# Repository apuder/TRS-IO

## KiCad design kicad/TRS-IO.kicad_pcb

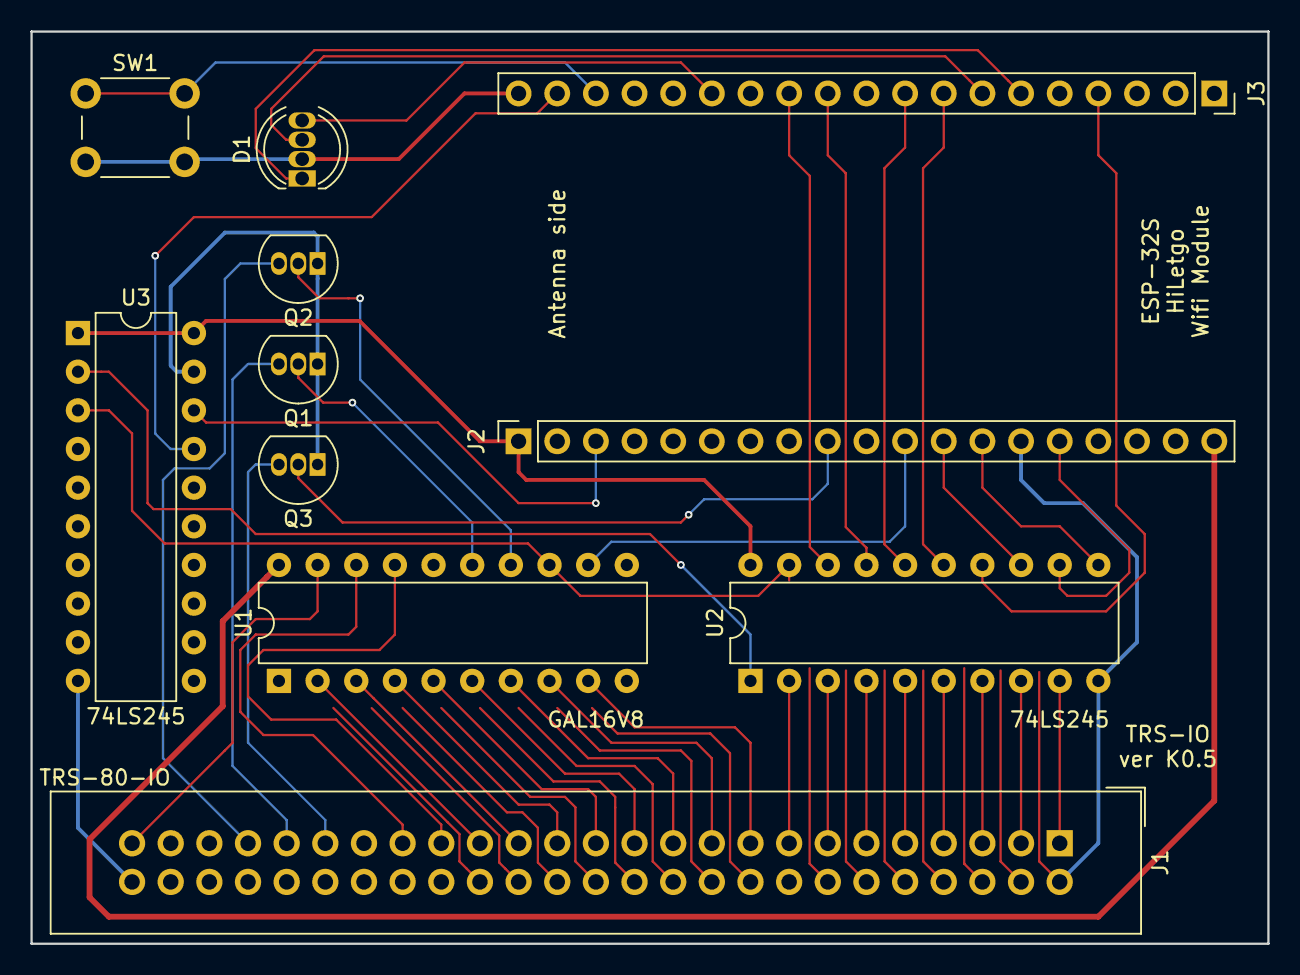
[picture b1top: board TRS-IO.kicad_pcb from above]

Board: 2 copper layers, 81.3 x 59.9 mm, 11 parts (0 on the bottom side), 45 nets.

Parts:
D1: LED_RCGB; LED_D5.0mm-4
J1: TRS-80-IO; IDC-Header_2x25_P2.54mm_Vertical
J2, J3: Conn_01x19; PinSocket_1x19_P2.54mm_Vertical
Q1, Q2, Q3: 2N7000; TO-92_Inline
SW1: SW_Push; SW_PUSH_6mm
U1: GAL16V8; DIP-20_W7.62mm
U2, U3: 74LS245; DIP-20_W7.62mm

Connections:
+3V3: J2.1, U2.20, U3.1, U3.20
+5V: J2.19, U1.20
GND: D1.2, J1.2, J1.4, J1.6, J1.8, J1.10, J1.12, J1.14, J1.16, J1.18, J1.20, J1.22, J1.24, J1.26, J1.28, J1.30, J1.32, J1.34, J1.36, J1.38, J1.40, J1.42, J1.44, J1.46, J1.48, J1.50, J2.14, J3.13, J3.19, Q1.1, Q2.1, Q3.1, SW1.2, U1.10, U2.10, U3.10, U3.19
unnamed: D1.1, J3.6
unnamed: D1.3, J3.7
unnamed: D1.4, J3.14
unnamed: J1.1, U2.9
unnamed: J1.3, U2.8
unnamed: J1.5, U2.7
unnamed: J1.7, U2.6
unnamed: J1.9, U2.5
unnamed: J1.11, U2.4
unnamed: J1.13, U2.3
unnamed: J1.15, U2.2
unnamed: J1.17, U1.9
unnamed: J1.19, U1.8
unnamed: J1.21, U1.7
unnamed: J1.23, U1.6
unnamed: J1.25, U1.5
unnamed: J1.27, U1.4
unnamed: J1.29, U1.3
unnamed: J1.31, U1.2
unnamed: J1.33, U1.17
unnamed: J1.35, U1.18
unnamed: J1.39, Q3.3
unnamed: J1.41, Q1.3
unnamed: J1.43, Q2.3
unnamed: J1.49, U1.19
unnamed: J2.3, U3.18
unnamed: J2.9, Q3.2
unnamed: J2.11, U1.12
unnamed: J2.12, U2.13
unnamed: J2.13, U2.11
unnamed: J2.15, U2.12
unnamed: J3.4, U2.14
unnamed: J3.8, U2.15
unnamed: J3.9, U2.16
unnamed: J3.11, U2.17
unnamed: J3.12, U2.18
unnamed: J3.17, SW1.1
unnamed: J3.18, U3.17
unnamed: Q1.2, U1.15
unnamed: Q2.2, U1.14
unnamed: U1.13, U2.19, U3.3
unnamed: U2.1, U3.2

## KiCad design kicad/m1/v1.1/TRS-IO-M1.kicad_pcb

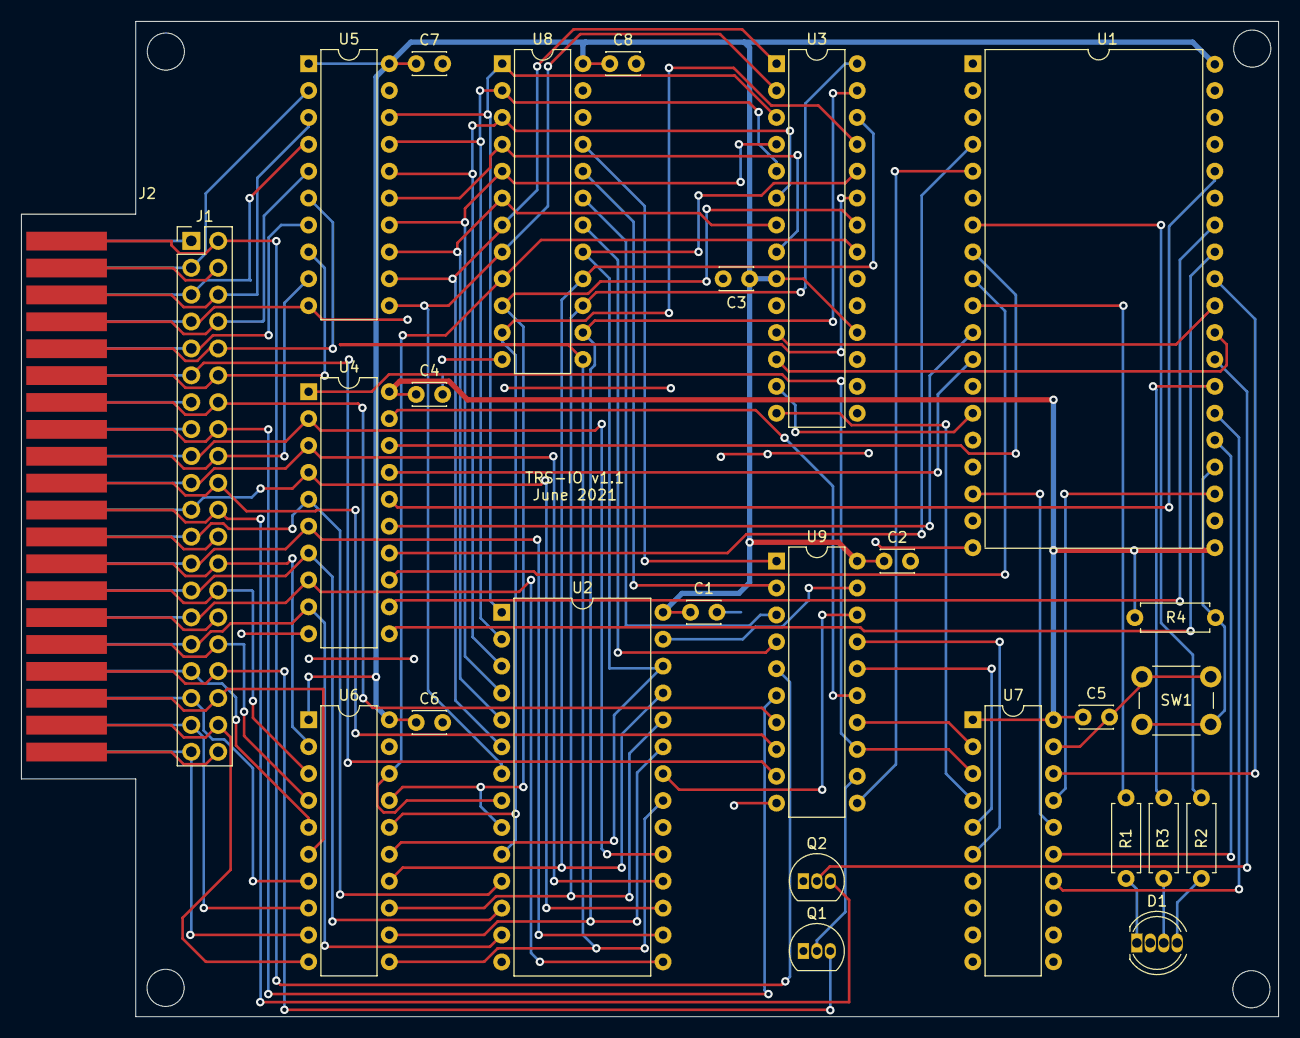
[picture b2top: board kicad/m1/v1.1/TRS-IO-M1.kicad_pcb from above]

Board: 2 copper layers, 118.7 x 94.0 mm, 27 parts (0 on the bottom side), 94 nets.

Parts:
C1, C2, C3, C4, C5, C6, C7, C8: 0.1uF; C_Disc_D3.0mm_W2.0mm_P2.50mm
D1: LED_RCBG; LED_D5.0mm-4_RGB
J1: Conn_02x20_Odd_Even; PinHeader_2x20_P2.54mm_Vertical
J2: Conn_02x20_Odd_Even; TRSEDGE
Q1, Q2: 2N7000; TO-92_Inline
R1, R2, R3: 100; R_Axial_DIN0207_L6.3mm_D2.5mm_P7.62mm_Horizontal
R4: 4K7; R_Axial_DIN0207_L6.3mm_D2.5mm_P7.62mm_Horizontal
SW1: SW_Push; SW_PUSH_6mm_H9.5mm
U1: HiLetgo-ESP-32S; DIP-38_W22.9mm
U2: AS6C62256-PDIP; DIP-28_W15.24mm
U3: MCP23S17_SP; DIP-28_W7.62mm
U4, U5, U6, U7: 74LVC245; DIP-20_W7.62mm
U8: ATF22V10-PDIP; DIP-24_W7.62mm
U9: ATF16V8-PDIP; DIP-20_W7.62mm

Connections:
5V: J1.40, J2.40
+3V3: C4.1, C5.1, R4.1, U1.20, U4.20, U7.1, U7.20
+5V: C1.1, C2.1, C3.1, C6.1, C7.1, C8.1, U1.38, U2.28, U3.9, U3.18, U5.1, U5.20, U6.1, U6.20, U8.24, U9.20
A0: J1.26, J2.26, U6.2
A1: J1.28, J2.28, U6.3
A2: J1.39, J2.39, U6.9
A3: J1.33, J2.33, U6.5
A4: J1.32, J2.32, U6.4
A5: J1.36, J2.36, U6.6
A6: J1.37, J2.37, U6.8
A7: J1.35, J2.35, U6.7
A8: J1.12, J2.12, U5.8
A9: J1.18, J2.18, U5.9
A10: J1.3, J2.3, U5.2
A11: J1.10, J2.10, U5.6
A12: J1.6, J2.6, U5.3
A13: J1.5, J2.5, U5.4
A14: J1.9, J2.9, U5.7
A15: J1.8, J2.8, U5.5
AA0: U2.8, U3.21, U6.18, U8.9
AA1: U2.9, U3.22, U6.17, U8.10
AA2: U2.21, U3.23, U6.11, U8.13
AA3: U2.26, U3.24, U6.15, U8.17
AA4: U2.10, U3.25, U6.16, U8.11
AA5: U2.25, U3.26, U6.14, U8.16
AA6: U2.23, U3.27, U6.12, U8.14
AA7: U2.24, U3.28, U6.13, U8.15
AA8: U2.6, U3.1, U5.12, U8.7
AA9: U2.7, U3.2, U5.11, U8.8
AA10: U2.1, U3.3, U5.18, U8.1
AA11: U2.4, U3.4, U5.14, U8.5
AA12: U2.2, U3.5, U5.17, U8.2
AA13: U2.3, U3.6, U5.16, U8.3
AA14: U2.5, U3.7, U5.13, U8.6
AA15: U3.8, U5.15, U8.4
ADDR_0: U8.19, U9.3
ADDR_1: U8.18, U9.4
ADDR_FREHD: U8.20, U9.2
ADDR_TRS_IO: U8.21, U9.1
BUTTON: R4.2, SW1.2, U1.23
CAS_N: J1.4, J2.4
CS23S17: U1.29, U3.11
D0: J1.29, J2.29, U2.15, U4.8
D1: J1.21, J2.21, U2.17, U4.4
D2: J1.31, J2.31, U2.13, U4.9
D3: J1.25, J2.25, U2.16, U4.6
D4: J1.17, J2.17, U2.19, U4.2
D5: J1.27, J2.27, U2.12, U4.7
D6: J1.23, J2.23, U2.11, U4.5
D7: J1.19, J2.19, U2.18, U4.3
DBUS_SEL_N: U4.19, U9.15
DD0: U1.32, U4.12
DD1: U1.34, U4.16
DD2: U1.31, U4.11
DD3: U1.4, U4.14
DD4: U1.8, U4.18
DD5: U1.9, U4.13
DD6: U1.11, U4.15
DD7: U1.12, U4.17
ESP3_SEL_N: U1.30, U7.18
ESP_INT: Q2.2, U1.27
ESP_MISO: U1.17, U7.16
ESP_READ_N: U1.22, U7.17
ESP_S0: U1.24, U7.15
ESP_S1: U1.25, U7.14
ESP_SEL_N: U7.2, U9.14
ESP_WAIT_RELEASE_N: U1.5, U9.11
GND: C1.2, C2.2, C3.2, C4.2, C5.2, C6.2, C7.2, C8.2, D1.2, J1.7, J1.30, J1.38, J2.7, J2.30, J2.38, Q1.1, Q2.1, SW1.1, U1.13, U1.19, U1.33, U2.14, U2.20, U3.10, U3.15, U3.16, U3.17, U4.10, U5.10, U5.19, U6.10, U6.19, U7.10, U7.19, U8.12, U9.10
INTACK_N: J1.13, J2.13
INT_N: J1.22, J2.22, Q2.3
IN_N: J1.20, J2.20, U9.8
LED_BLUE: R3.1, U1.26
LED_GREEN: R2.1, U1.7
LED_RED: R1.1, U1.10
MISO: U3.14, U7.4
MOSI: U1.14, U3.13
MUX: J1.15, J2.15
unnamed: D1.1, R1.2
unnamed: D1.3, R3.2
unnamed: D1.4, R2.2
OUT_N: J1.11, J2.11, U9.9
RAS_N: J1.2, J2.2, U9.5
RD_N: J1.16, J2.16, U9.6
READ_N: U4.1, U7.3, U9.13
S0: U7.5, U9.16
S1: U7.6, U9.17
SCK: U1.28, U3.12
SRAM_OE_N: U2.22, U9.18
SRAM_WE_N: U2.27, U9.19
SYSRES_N: J1.1, J2.1
TEST_N: J1.24, J2.24
WAIT: Q1.2, U9.12
WAIT_N: J1.34, J2.34, Q1.3
WR_N: J1.14, J2.14, U9.7

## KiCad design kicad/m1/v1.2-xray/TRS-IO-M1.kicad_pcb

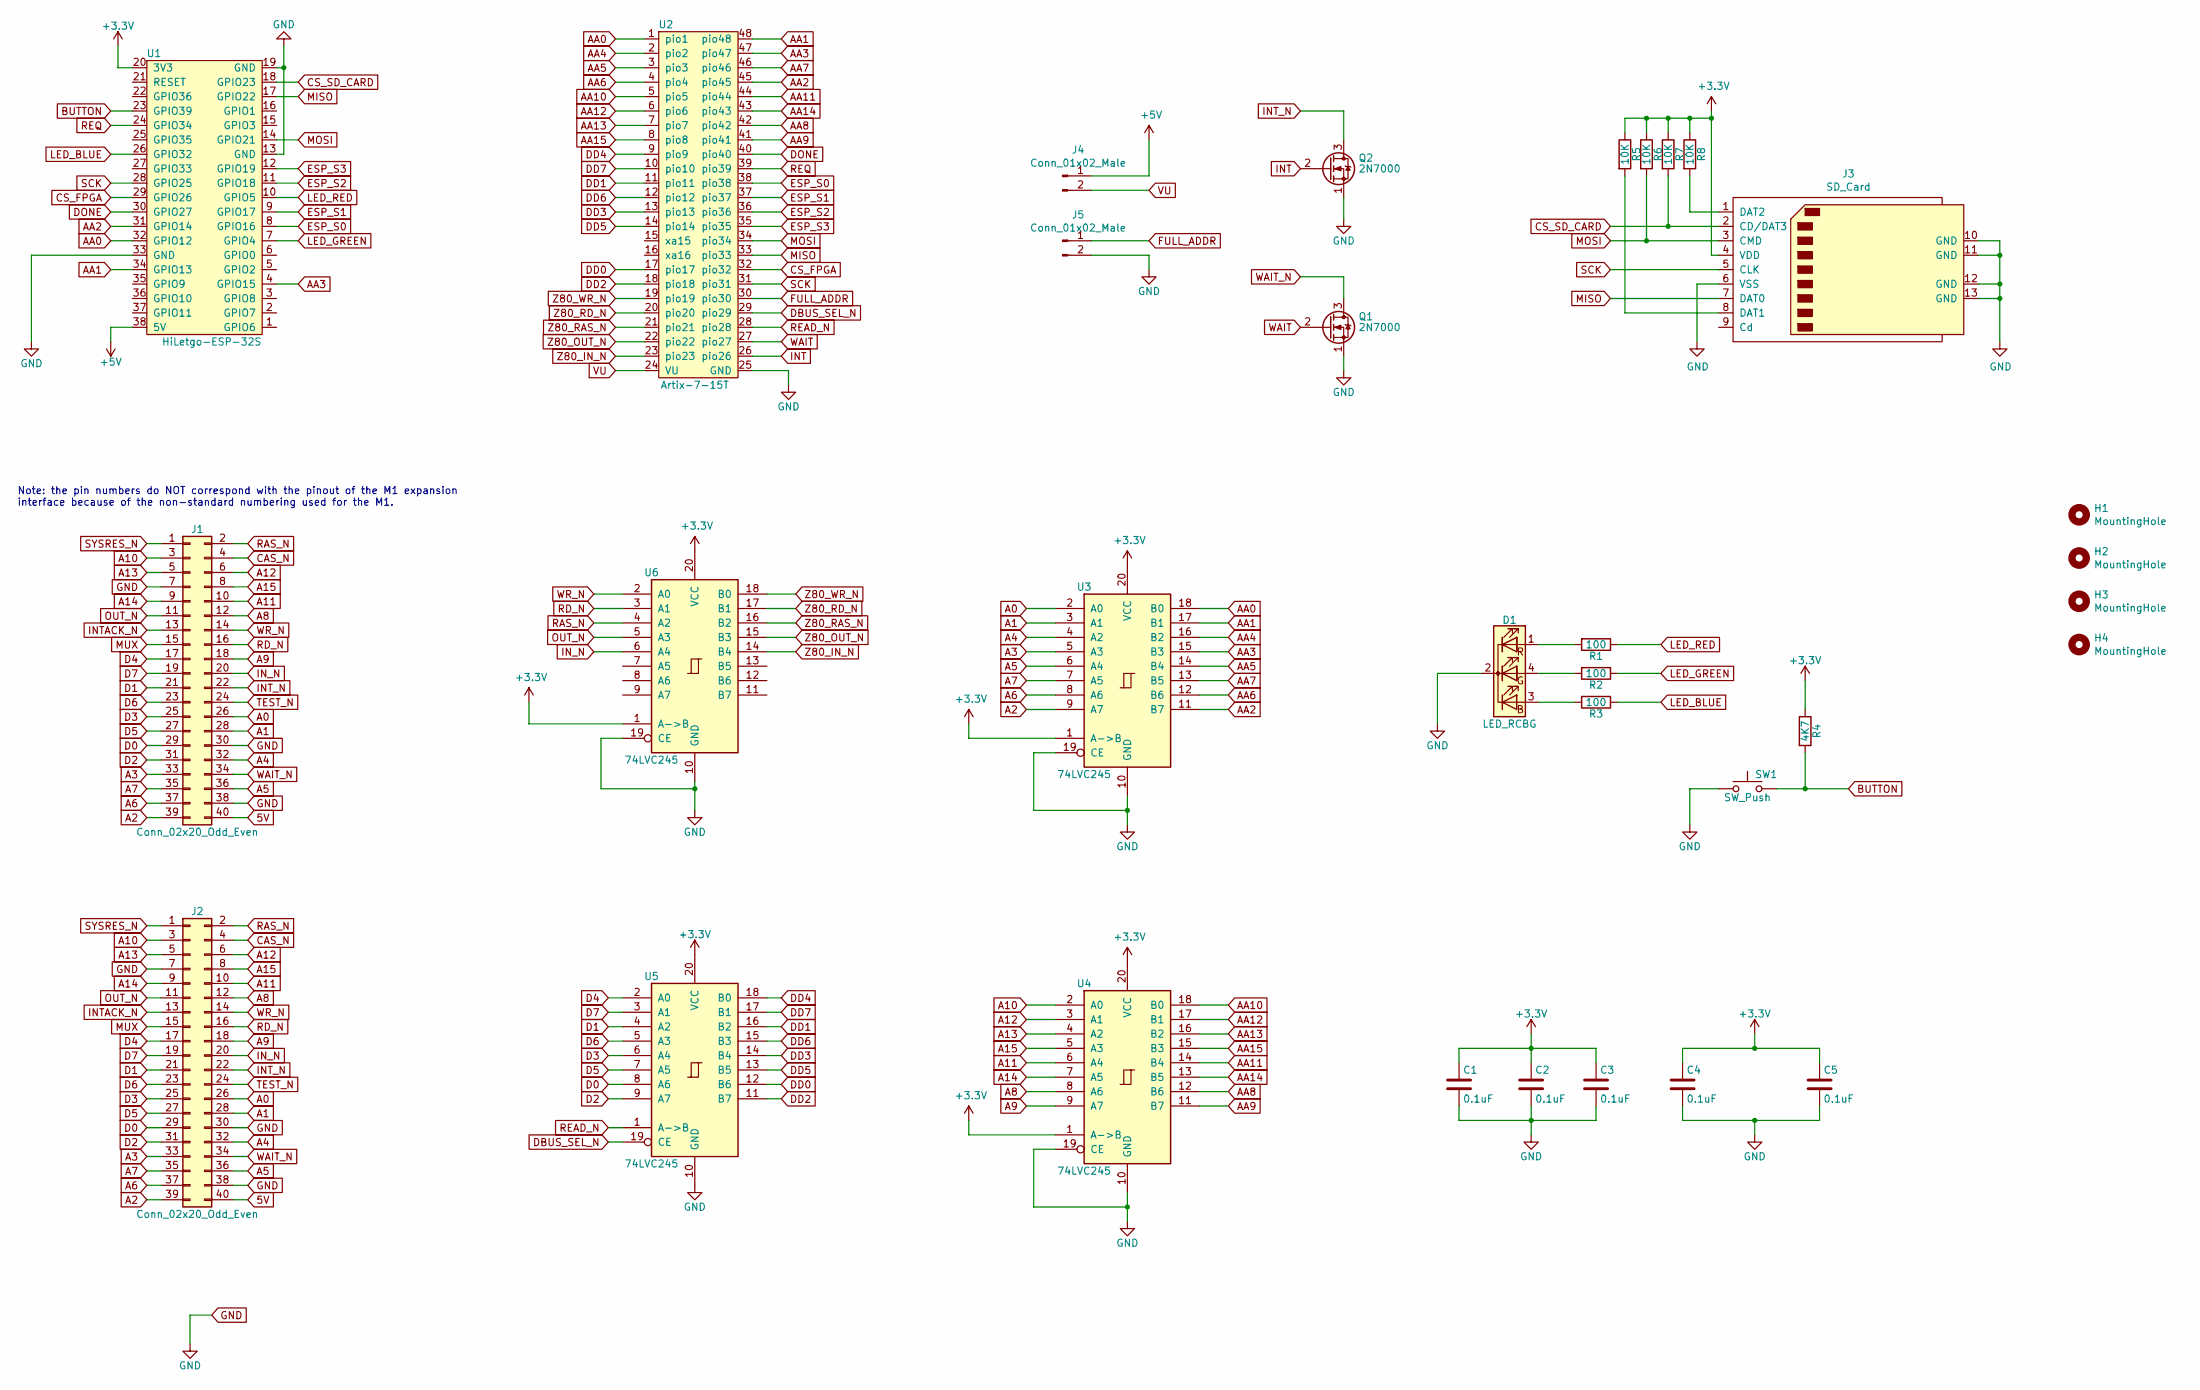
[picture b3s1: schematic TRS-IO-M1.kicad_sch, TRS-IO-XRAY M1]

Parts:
C1, C2, C3, C4, C5: 0.1uF; C_Disc_D3.0mm_W2.0mm_P2.50mm
D1: LED_RCBG; LED_D5.0mm-4_RGB
H1, H2, H3, H4: MountingHole; MountingHole_2.5mm_Pad_Via
J1: Conn_02x20_Odd_Even; PinHeader_2x20_P2.54mm_Vertical
J2: Conn_02x20_Odd_Even; TRSEDGE
J3: SD_Card; TFP09-2-12B
J4, J5: Conn_01x02_Male; PinHeader_1x02_P2.54mm_Vertical
Q1, Q2: 2N7000; TO-92_Inline
R1, R2, R3: 100; R_Axial_DIN0207_L6.3mm_D2.5mm_P7.62mm_Horizontal
R4: 4K7; R_Axial_DIN0207_L6.3mm_D2.5mm_P7.62mm_Horizontal
R5, R6, R7, R8: 10K; R_Axial_DIN0207_L6.3mm_D2.5mm_P7.62mm_Horizontal
SW1: SW_Push; SW_PUSH_6mm_H9.5mm
U1: HiLetgo-ESP-32S; DIP-38_W22.9mm
U2: Artix-7-15T; DIP-48_600_ELL
U3, U4, U5, U6: 74LVC245; DIP-20_W7.62mm

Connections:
5V: J1.40, J2.40
+3V3: C1.1, C2.1, C3.1, C4.1, C5.1, J3.4 (VDD), R4.1, R5.1, R6.1, R7.1, R8.1, U1.20 (3V3), U3.1 (A->B), U3.20 (VCC), U4.1 (A->B), U4.20 (VCC), U5.20 (VCC), U6.1 (A->B), U6.20 (VCC)
+5V: J4.1, U1.38 (5V)
A0: J1.26, J2.26, U3.2 (A0)
A1: J1.28, J2.28, U3.3 (A1)
A2: J1.39, J2.39, U3.9 (A7)
A3: J1.33, J2.33, U3.5 (A3)
A4: J1.32, J2.32, U3.4 (A2)
A5: J1.36, J2.36, U3.6 (A4)
A6: J1.37, J2.37, U3.8 (A6)
A7: J1.35, J2.35, U3.7 (A5)
A8: J1.12, J2.12, U4.8 (A6)
A9: J1.18, J2.18, U4.9 (A7)
A10: J1.3, J2.3, U4.2 (A0)
A11: J1.10, J2.10, U4.6 (A4)
A12: J1.6, J2.6, U4.3 (A1)
A13: J1.5, J2.5, U4.4 (A2)
A14: J1.9, J2.9, U4.7 (A5)
A15: J1.8, J2.8, U4.5 (A3)
AA0: U1.32 (GPIO12), U2.1 (pio1), U3.18 (B0)
AA1: U1.34 (GPIO13), U2.48 (pio48), U3.17 (B1)
AA2: U1.31 (GPIO14), U2.45 (pio45), U3.11 (B7)
AA3: U1.4 (GPIO15), U2.47 (pio47), U3.15 (B3)
AA4: U2.2 (pio2), U3.16 (B2)
AA5: U2.3 (pio3), U3.14 (B4)
AA6: U2.4 (pio4), U3.12 (B6)
AA7: U2.46 (pio46), U3.13 (B5)
AA8: U2.42 (pio42), U4.12 (B6)
AA9: U2.41 (pio41), U4.11 (B7)
AA10: U2.5 (pio5), U4.18 (B0)
AA11: U2.44 (pio44), U4.14 (B4)
AA12: U2.6 (pio6), U4.17 (B1)
AA13: U2.7 (pio7), U4.16 (B2)
AA14: U2.43 (pio43), U4.13 (B5)
AA15: U2.8 (pio8), U4.15 (B3)
BUTTON: R4.2, SW1.2, U1.23 (GPIO39)
CAS_N: J1.4, J2.4
CS_FPGA: U1.29 (GPIO26), U2.32 (pio32)
CS_SD_CARD: J3.2 (CD/DAT3), R7.2, U1.18 (GPIO23)
D0: J1.29, J2.29, U5.8 (A6)
D1: J1.21, J2.21, U5.4 (A2)
D2: J1.31, J2.31, U5.9 (A7)
D3: J1.25, J2.25, U5.6 (A4)
D4: J1.17, J2.17, U5.2 (A0)
D5: J1.27, J2.27, U5.7 (A5)
D6: J1.23, J2.23, U5.5 (A3)
D7: J1.19, J2.19, U5.3 (A1)
DBUS_SEL_N: U2.29 (pio29), U5.19 (CE)
DD0: U2.17 (pio17), U5.12 (B6)
DD1: U2.11 (pio11), U5.16 (B2)
DD2: U2.18 (pio18), U5.11 (B7)
DD3: U2.13 (pio13), U5.14 (B4)
DD4: U2.9 (pio9), U5.18 (B0)
DD5: U2.14 (pio14), U5.13 (B5)
DD6: U2.12 (pio12), U5.15 (B3)
DD7: U2.10 (pio10), U5.17 (B1)
DONE: U1.30 (GPIO27), U2.40 (pio40)
ESP_S0: U1.8 (GPIO16), U2.38 (pio38)
ESP_S1: U1.9 (GPIO17), U2.37 (pio37)
ESP_S2: U1.11 (GPIO18), U2.36 (pio36)
ESP_S3: U1.12 (GPIO19), U2.35 (pio35)
FULL_ADDR: J5.1, U2.30 (pio30)
GND: C1.2, C2.2, C3.2, C4.2, C5.2, D1.2 (K), J1.7, J1.30, J1.38, J2.7, J2.30, J2.38, J3.6 (VSS), J3.10 (GND), J3.11 (GND), J3.12 (GND), J3.13 (GND), J5.2, Q1.1 (S), Q2.1 (S), SW1.1, U1.13 (GND), U1.19 (GND), U1.33 (GND), U2.25 (GND), U3.10 (GND), U3.19 (CE), U4.10 (GND), U4.19 (CE), U5.10 (GND), U6.10 (GND), U6.19 (CE)
INT: Q2.2 (G), U2.26 (pio26)
INTACK_N: J1.13, J2.13
INT_N: J1.22, J2.22, Q2.3 (D)
IN_N: J1.20, J2.20, U6.6 (A4)
LED_BLUE: R3.1, U1.26 (GPIO32)
LED_GREEN: R2.1, U1.7 (GPIO4)
LED_RED: R1.1, U1.10 (GPIO5)
MISO: J3.7 (DAT0), U1.17 (GPIO22), U2.33 (pio33)
MOSI: J3.3 (CMD), R6.2, U1.14 (GPIO21), U2.34 (pio34)
MUX: J1.15, J2.15
unnamed: D1.1 (RA), R1.2
unnamed: D1.3 (BA), R3.2
unnamed: D1.4 (GA), R2.2
unnamed: J3.1 (DAT2), R8.2
unnamed: J3.8 (DAT1), R5.2
OUT_N: J1.11, J2.11, U6.5 (A3)
RAS_N: J1.2, J2.2, U6.4 (A2)
RD_N: J1.16, J2.16, U6.3 (A1)
READ_N: U2.28 (pio28), U5.1 (A->B)
REQ: U1.24 (GPIO34), U2.39 (pio39)
SCK: J3.5 (CLK), U1.28 (GPIO25), U2.31 (pio31)
SYSRES_N: J1.1, J2.1
TEST_N: J1.24, J2.24
VU: J4.2, U2.24 (VU)
WAIT: Q1.2 (G), U2.27 (pio27)
WAIT_N: J1.34, J2.34, Q1.3 (D)
WR_N: J1.14, J2.14, U6.2 (A0)
Z80_IN_N: U2.23 (pio23), U6.14 (B4)
Z80_OUT_N: U2.22 (pio22), U6.15 (B3)
Z80_RAS_N: U2.21 (pio21), U6.16 (B2)
Z80_RD_N: U2.20 (pio20), U6.17 (B1)
Z80_WR_N: U2.19 (pio19), U6.18 (B0)

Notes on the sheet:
Note: the pin numbers do NOT correspond with the pinout of the M1 expansion interface because of the non-standard numbering used for the M1.

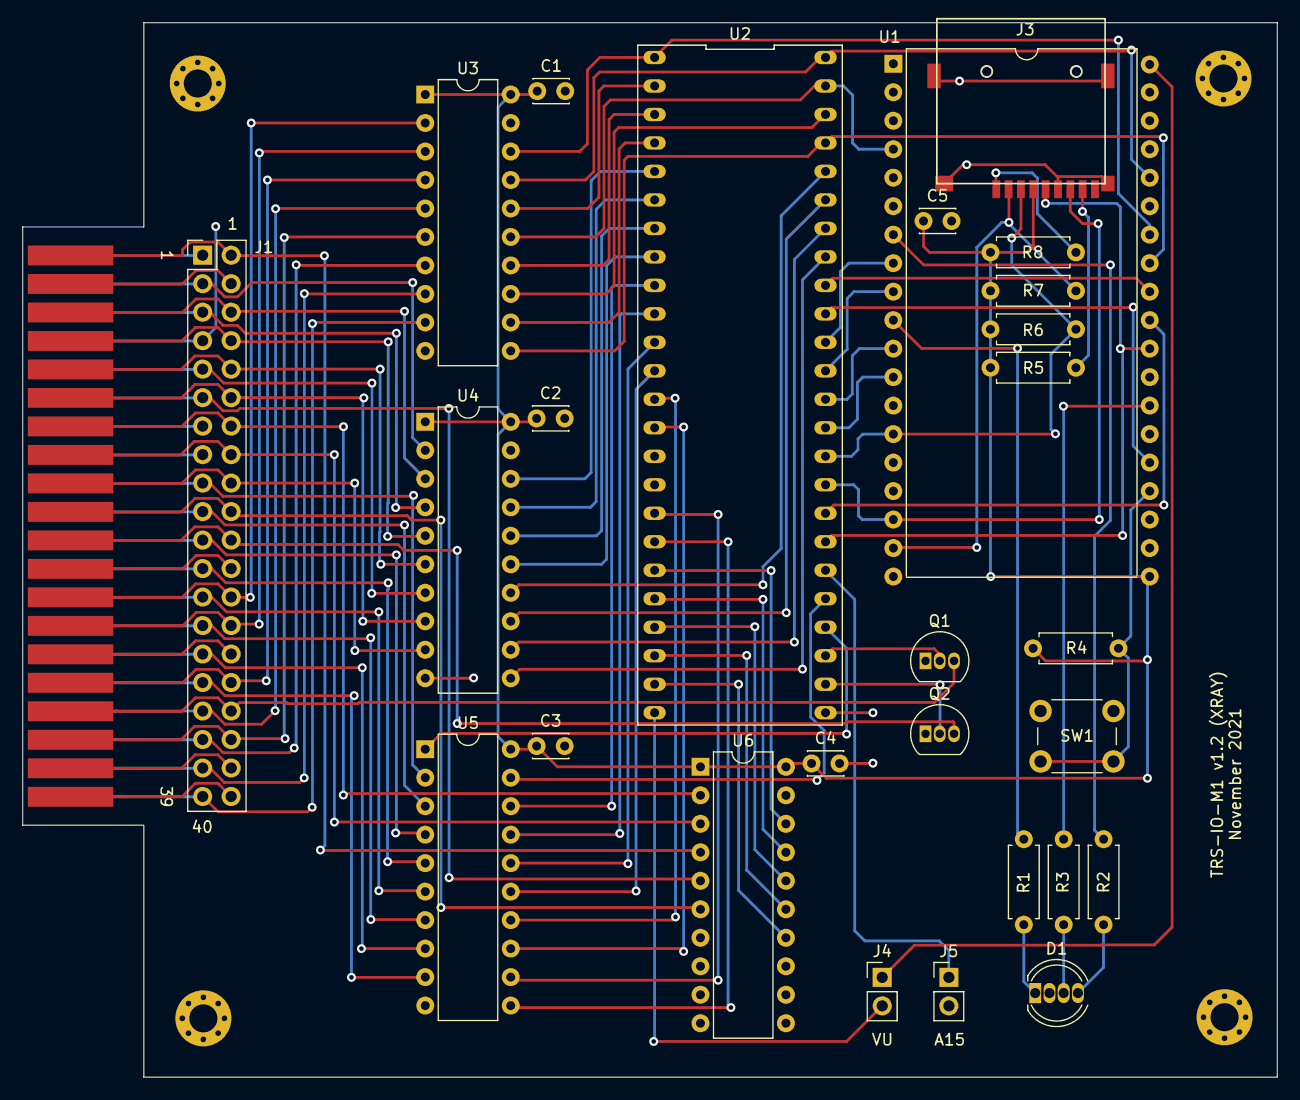
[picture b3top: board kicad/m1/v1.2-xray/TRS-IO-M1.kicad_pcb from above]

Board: 2 copper layers, 111.9 x 94.0 mm, 32 parts (0 on the bottom side), 95 nets.

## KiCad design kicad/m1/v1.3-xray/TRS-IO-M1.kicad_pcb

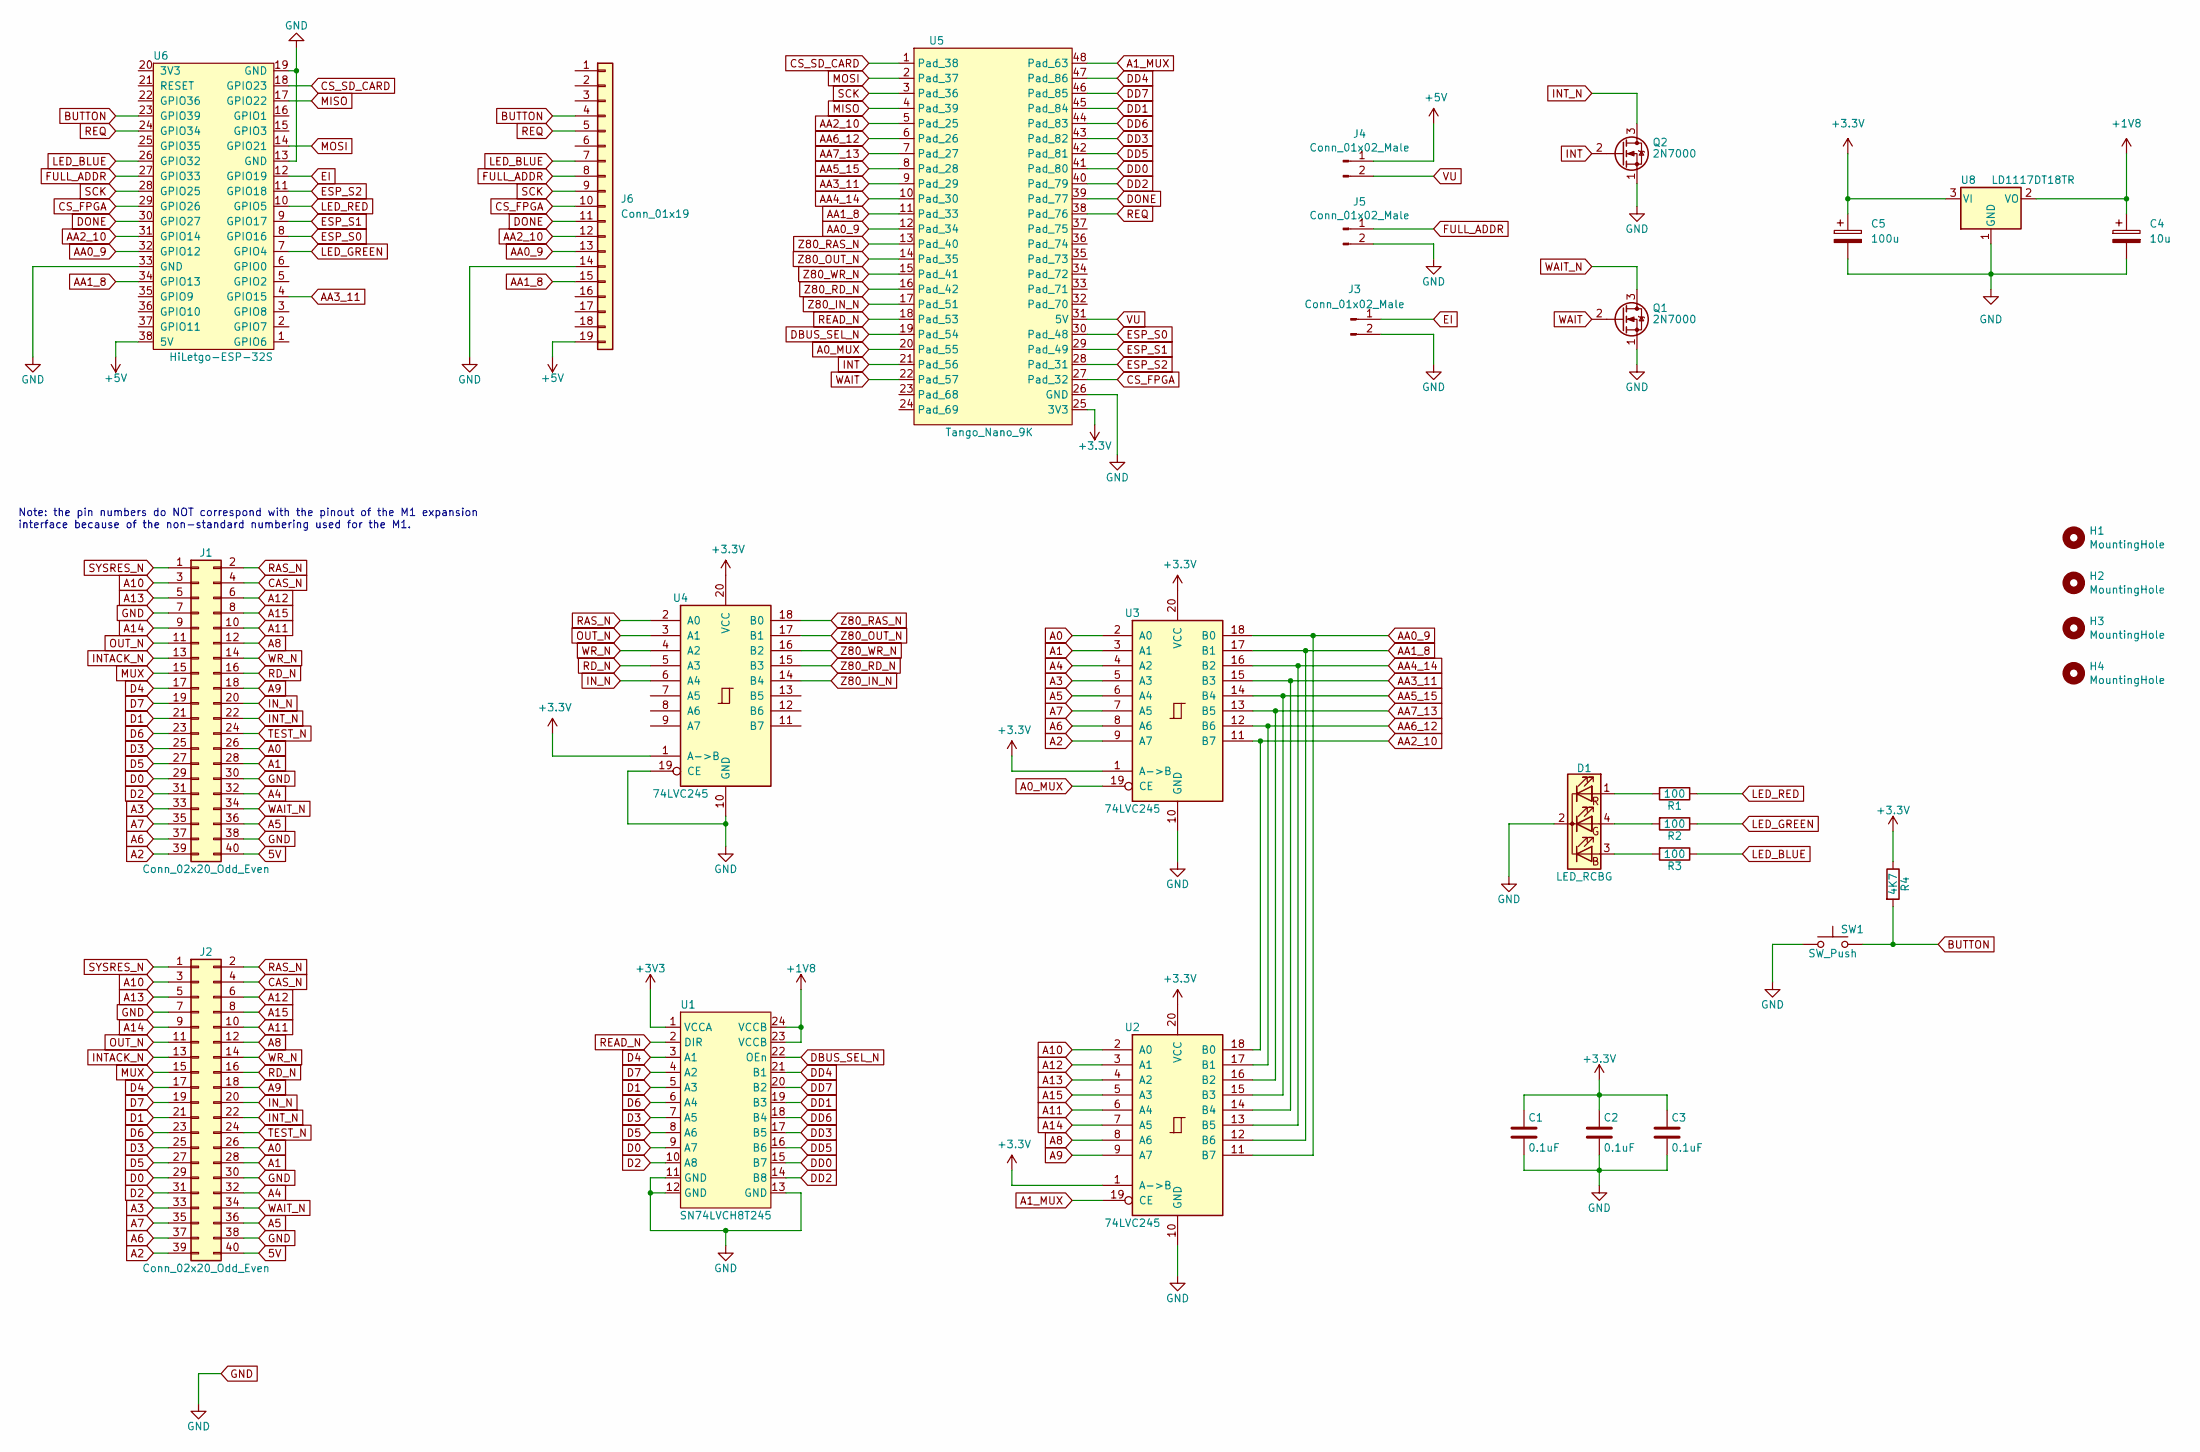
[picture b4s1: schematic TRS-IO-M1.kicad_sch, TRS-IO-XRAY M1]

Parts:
C1, C2, C3: 0.1uF; C_0805_2012Metric_Pad1.18x1.45mm_HandSolder
C4: 10u; C_1206_3216Metric_Pad1.33x1.80mm_HandSolder
C5: 100u; C_1206_3216Metric_Pad1.33x1.80mm_HandSolder
D1: LED_RCBG; LED_D5.0mm-4_RGB
H1, H2, H3, H4: MountingHole; MountingHole_3mm_Pad_Via
J1: Conn_02x20_Odd_Even; PinHeader_2x20_P2.54mm_Vertical
J2: Conn_02x20_Odd_Even; TRSEDGE
J3, J4, J5: Conn_01x02_Male; PinHeader_1x02_P2.54mm_Vertical
J6: Conn_01x19; PinHeader_1x19_P2.54mm_Vertical
Q1, Q2: 2N7000; TO-92_Inline
R1, R2, R3: 100; R_Axial_DIN0207_L6.3mm_D2.5mm_P7.62mm_Horizontal
R4: 4K7; R_Axial_DIN0207_L6.3mm_D2.5mm_P7.62mm_Horizontal
SW1: SW_Push; SW_PUSH_6mm_H9.5mm
U1: SN74LVCH8T245; TSSOP-24_4.4x7.8mm_P0.65mm
U2, U3, U4: 74LVC245; SSOP-20_5.3x7.2mm_P0.65mm
U5: Tango_Nano_9K; DIP-48_W22.9mm
U6: HiLetgo-ESP-32S; DIP-38_W22.9mm
U8: LD1117DT18TR; TO-252-3_TabPin2

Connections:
5V: J1.40, J2.40
+1V8: C4.1, U1.23 (VCCB), U1.24 (VCCB), U8.2 (VO)
+5V: J4.1, J6.19, U6.38 (5V)
A0: J1.26, J2.26, U3.2 (A0)
A0_MUX: U3.19 (CE), U5.20 (Pad_55)
A1: J1.28, J2.28, U3.3 (A1)
A1_MUX: U2.19 (CE), U5.48 (Pad_63)
A2: J1.39, J2.39, U3.9 (A7)
A3: J1.33, J2.33, U3.5 (A3)
A4: J1.32, J2.32, U3.4 (A2)
A5: J1.36, J2.36, U3.6 (A4)
A6: J1.37, J2.37, U3.8 (A6)
A7: J1.35, J2.35, U3.7 (A5)
A8: J1.12, J2.12, U2.8 (A6)
A9: J1.18, J2.18, U2.9 (A7)
A10: J1.3, J2.3, U2.2 (A0)
A11: J1.10, J2.10, U2.6 (A4)
A12: J1.6, J2.6, U2.3 (A1)
A13: J1.5, J2.5, U2.4 (A2)
A14: J1.9, J2.9, U2.7 (A5)
A15: J1.8, J2.8, U2.5 (A3)
AA0_9: J6.13, U2.11 (B7), U3.18 (B0), U5.12 (Pad_34), U6.32 (GPIO12)
AA1_8: J6.15, U2.12 (B6), U3.17 (B1), U5.11 (Pad_33), U6.34 (GPIO13)
AA2_10: J6.12, U2.18 (B0), U3.11 (B7), U5.5 (Pad_25), U6.31 (GPIO14)
AA3_11: U2.14 (B4), U3.15 (B3), U5.9 (Pad_29), U6.4 (GPIO15)
AA4_14: U2.13 (B5), U3.16 (B2), U5.10 (Pad_30)
AA5_15: U2.15 (B3), U3.14 (B4), U5.8 (Pad_28)
AA6_12: U2.17 (B1), U3.12 (B6), U5.6 (Pad_26)
AA7_13: U2.16 (B2), U3.13 (B5), U5.7 (Pad_27)
BUTTON: J6.4, R4.2, SW1.2, U6.23 (GPIO39)
CAS_N: J1.4, J2.4
CS_FPGA: J6.10, U5.27 (Pad_32), U6.29 (GPIO26)
CS_SD_CARD: U5.1 (Pad_38), U6.18 (GPIO23)
D0: J1.29, J2.29, U1.9 (A7)
D1: J1.21, J2.21, U1.5 (A3)
D2: J1.31, J2.31, U1.10 (A8)
D3: J1.25, J2.25, U1.7 (A5)
D4: J1.17, J2.17, U1.3 (A1)
D5: J1.27, J2.27, U1.8 (A6)
D6: J1.23, J2.23, U1.6 (A4)
D7: J1.19, J2.19, U1.4 (A2)
DBUS_SEL_N: U1.22 (OEn), U5.19 (Pad_54)
DD0: U1.15 (B7), U5.41 (Pad_80)
DD1: U1.19 (B3), U5.45 (Pad_84)
DD2: U1.14 (B8), U5.40 (Pad_79)
DD3: U1.17 (B5), U5.43 (Pad_82)
DD4: U1.21 (B1), U5.47 (Pad_86)
DD5: U1.16 (B6), U5.42 (Pad_81)
DD6: U1.18 (B4), U5.44 (Pad_83)
DD7: U1.20 (B2), U5.46 (Pad_85)
DONE: J6.11, U5.39 (Pad_77), U6.30 (GPIO27)
EI: J3.1, U6.12 (GPIO19)
ESP_S0: U5.30 (Pad_48), U6.8 (GPIO16)
ESP_S1: U5.29 (Pad_49), U6.9 (GPIO17)
ESP_S2: U5.28 (Pad_31), U6.11 (GPIO18)
FULL_ADDR: J5.1, J6.8, U6.27 (GPIO33)
GND: C1.2, C2.2, C3.2, C4.2, C5.2, D1.2 (K), J1.7, J1.30, J1.38, J2.7, J2.30, J2.38, J3.2, J5.2, J6.14, Q1.1 (S), Q2.1 (S), SW1.1, U1.11 (GND), U1.12 (GND), U1.13 (GND), U2.10 (GND), U3.10 (GND), U4.10 (GND), U4.19 (CE), U5.26 (GND), U6.13 (GND), U6.19 (GND), U6.33 (GND), U8.1 (GND)
INT: Q2.2 (G), U5.21 (Pad_56)
INTACK_N: J1.13, J2.13
INT_N: J1.22, J2.22, Q2.3 (D)
IN_N: J1.20, J2.20, U4.6 (A4)
LED_BLUE: J6.7, R3.1, U6.26 (GPIO32)
LED_GREEN: R2.1, U6.7 (GPIO4)
LED_RED: R1.1, U6.10 (GPIO5)
MISO: U5.4 (Pad_39), U6.17 (GPIO22)
MOSI: U5.2 (Pad_37), U6.14 (GPIO21)
MUX: J1.15, J2.15
unnamed: D1.1 (RA), R1.2
unnamed: D1.3 (BA), R3.2
unnamed: D1.4 (GA), R2.2
OUT_N: J1.11, J2.11, U4.3 (A1)
RAS_N: J1.2, J2.2, U4.2 (A0)
RD_N: J1.16, J2.16, U4.5 (A3)
READ_N: U1.2 (DIR), U5.18 (Pad_53)
REQ: J6.5, U5.38 (Pad_76), U6.24 (GPIO34)
SCK: J6.9, U5.3 (Pad_36), U6.28 (GPIO25)
SYSRES_N: J1.1, J2.1
TEST_N: J1.24, J2.24
VU: J4.2, U5.31 (5V)
WAIT: Q1.2 (G), U5.22 (Pad_57)
WAIT_N: J1.34, J2.34, Q1.3 (D)
WR_N: J1.14, J2.14, U4.4 (A2)
Z80_IN_N: U4.14 (B4), U5.17 (Pad_51)
Z80_OUT_N: U4.17 (B1), U5.14 (Pad_35)
Z80_RAS_N: U4.18 (B0), U5.13 (Pad_40)
Z80_RD_N: U4.15 (B3), U5.16 (Pad_42)
Z80_WR_N: U4.16 (B2), U5.15 (Pad_41)

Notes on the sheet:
Note: the pin numbers do NOT correspond with the pinout of the M1 expansion interface because of the non-standard numbering used for the M1.

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
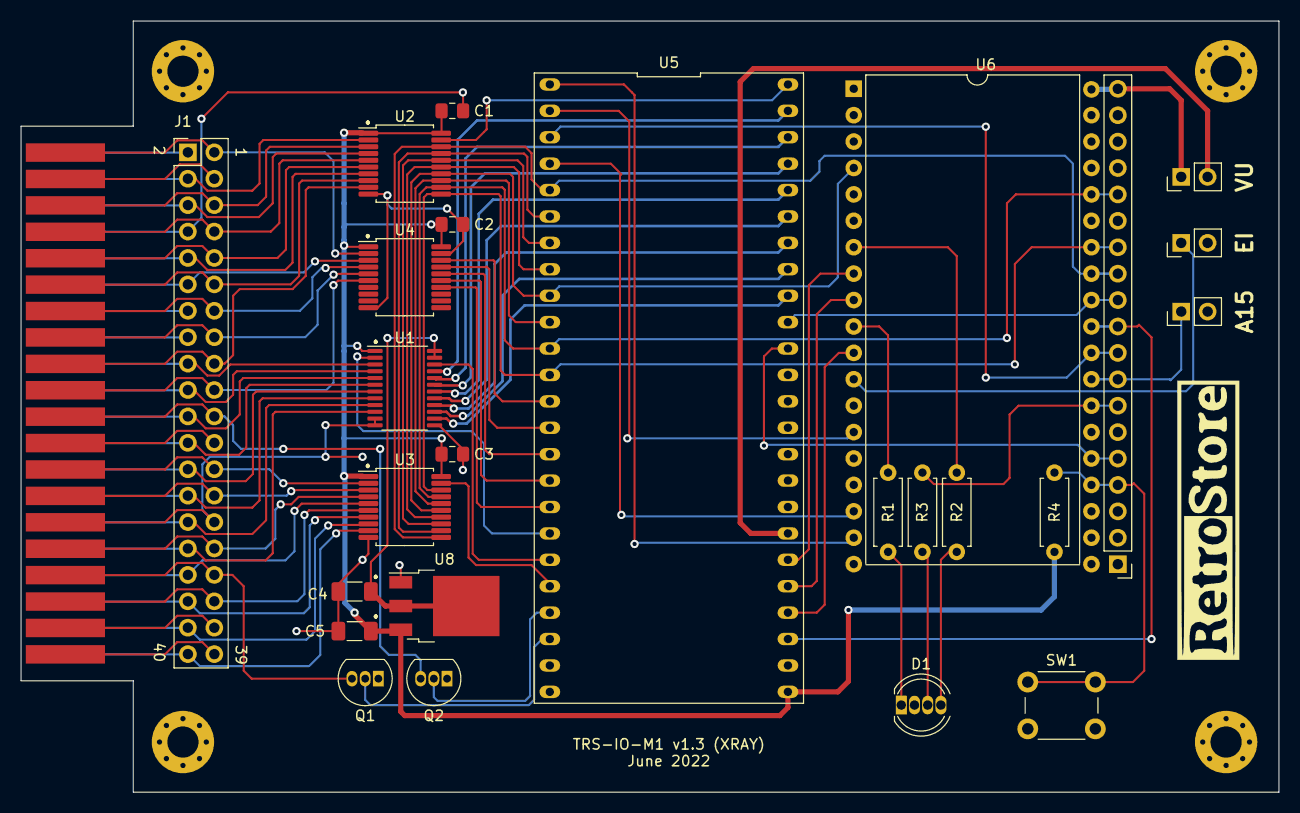
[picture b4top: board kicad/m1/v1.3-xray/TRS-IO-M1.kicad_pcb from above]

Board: 2 copper layers, 121.0 x 74.2 mm, 31 parts (0 on the bottom side), 88 nets.

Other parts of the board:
G1: LOGO
